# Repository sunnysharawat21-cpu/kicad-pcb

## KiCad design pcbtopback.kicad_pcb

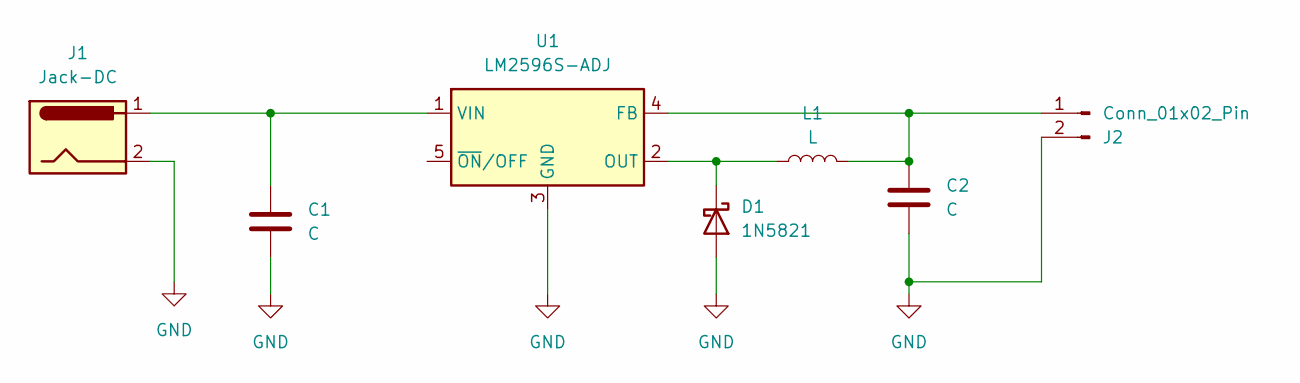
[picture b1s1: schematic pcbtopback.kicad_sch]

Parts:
C1: C; CP_Elec_5x5.9
C2: C; CP_Elec_5x5.3
D1: 1N5821; D_T-1_P2.54mm_Vertical_AnodeUp
J1: Jack-DC; BarrelJack_SwitchcraftConxall_RAPC10U_Horizontal
J2: Conn_01x02_Pin; JST_EH_B2B-EH-A_1x02_P2.50mm_Vertical
L1: L; L_Radial_L12.6mm_W12.6mm_Px9.52mm_Py9.52mm_Pulse_LP-37
U1: LM2596S-ADJ; TO-263-5_TabPin3

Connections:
GND: C1.2, C2.2, D1.2 (A), J1.2, J2.2, U1.3 (GND)
unnamed: D1.1 (K), L1.1, U1.2 (OUT)
unnamed: C2.1, J2.1, L1.2, U1.4 (FB)
unnamed: C1.1, J1.1, U1.1 (VIN)

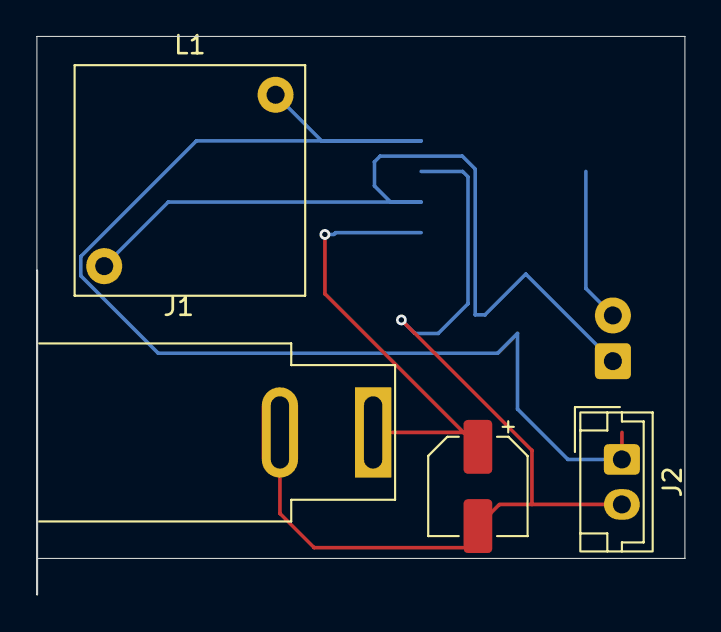
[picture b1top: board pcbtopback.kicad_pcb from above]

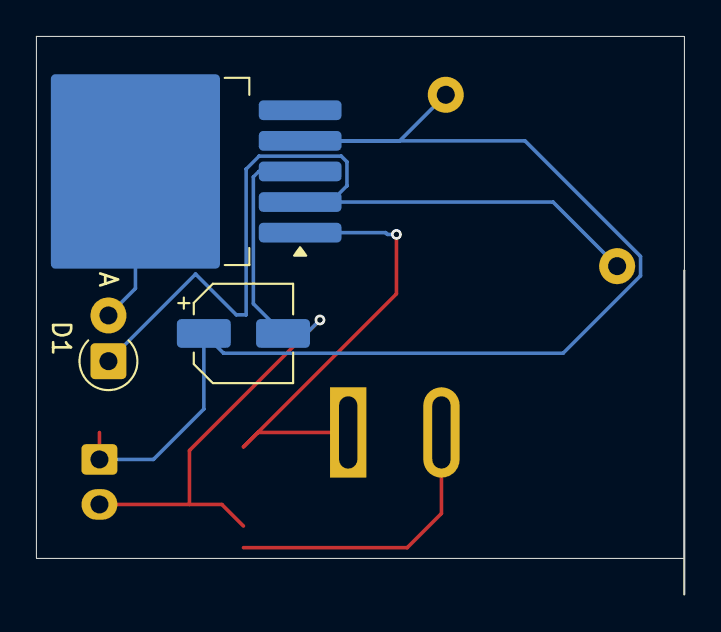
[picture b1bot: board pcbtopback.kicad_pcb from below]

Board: 2 copper layers, 36.0 x 31.0 mm, 7 parts (3 on the bottom side), 4 nets.
